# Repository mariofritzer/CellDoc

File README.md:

# CellDoc

**Diagnose für Akkuzellen.** Ein ESP32-Prüfstand, der Akkus lädt, mit konstantem Strom entlädt, dabei Kapazität, Energie und Innenwiderstand misst und am Ende eine **Lebenszahl von 0 bis 100** ausgibt. Bedient wird alles über eine Weboberfläche im Browser, am Handy wie am PC.

<picture>
  <source media="(prefers-color-scheme: dark)" srcset="docs/img/live-desktop-dark.png">
  
</picture>

> **Ausprobieren ohne Hardware:** [Demo im Browser](https://mariofritzer.github.io/CellDoc/) (Beispielwerte) · **Installieren:** [Webflasher](https://mariofritzer.github.io/CellDoc/flash/)

## Was CellDoc kann

- **Kapazitätstest** in einem Durchgang: voll laden → ruhen → mit Konstantstrom entladen → erholen → wieder voll oder auf Lagerspannung laden
- **Innenwiderstand (DC)** per Stromsprung, mehrmals während der Entladung, ausgewertet bei 100 % und 50 % Ladung
- **Lebenszahl** aus Kapazität und Innenwiderstand, mit Zelltyp-Datenbank und Schätzmodus für unbekannte Zellen
- **Zwei Anschlüsse:** A für Einzelzellen (laden und entladen), B für Packs bis 6S mit Balancer-Messung jeder Einzelzelle
- **Akkutypen:** Li-Ion, LiPo, Li-HV, LiFePO4, LTO, NiMH/NiCd und Blei
- **Bis 30 W / 8 A** Entladeleistung mit zwei Lastkanälen und Lüfter
- **Sicherheit:** drei Temperaturfühler mit Drosselung und Abschaltung, Über- und Unterspannung pro Zelle, Überstrom, Lüfter- und Sensorausfall, Not-Aus-Taste
- **Ergebnisse** mit Entladekurve, Ri-Verlauf und Vergleich zum ersten Test derselben Zelle
- **Zellenbestand** mit fester Nummer je Zelle (CD-0042), Suche nach Nummer, Name, Lagerort oder Notiz und Note A–D
- **Etiketten** mit Nummer, QR-Code und Messwerten als Bild für Etikettendrucker wie Supvan E16 oder Niimbot
- **Selbstentladungstest** über 7–14 Tage, findet Zellen mit innerem Kurzschluss
- **Pack zusammenstellen:** sucht gleich starke Zellen für z. B. 10S4P, verteilt sie gleichmäßig auf die Parallelgruppen und zeichnet einen druckbaren Bauplan mit Nickelbändern und Balancer-Abgriffen
- **Zyklentest** mit Kapazität je Zyklus, **Kurvenvergleich** mehrerer Tests und **Spannungscheck** beim Wiedereinstecken einer Zelle
- **Mehrere Geräte, ein Bestand:** CellDoc und Mini im selben WLAN teilen sich Zellen und Nummern
- **Home Assistant** über MQTT mit automatischer Erkennung, **Datensicherung** und CSV-Export
- **Handbuch** direkt im Gerät: Akkutypen, Bauformen, Stecker, Messwerte, Sicherheit, Lagerung und Entsorgung
- **Display und Taster** (optional, wie bei der Mini): Messwerte, Temperaturen, Balancer, IP-Adresse; Test starten und stoppen direkt am Gerät
- **Firmware-Updates** über den Browser, WLAN-Einrichtung direkt im Webflasher oder über einen eigenen Hotspot

## Bilder

| Live | Ergebnisse | Ergebnis im Detail |
|:---:|:---:|:---:|
|  |  |  |

| Test starten | Handbuch | Einstellungen |
|:---:|:---:|:---:|
|  |  |  |

*Fotos vom fertigen Aufbau folgen.*

## Zellenbestand und Etiketten

Jeder Test legt die Zelle mit einer festen Nummer an. Die Nummer kommt mit einem Etikettendrucker auf die Zelle, der QR-Code darauf öffnet die Zelle später direkt in CellDoc. Beim nächsten Test wird sie aus dem Bestand gewählt und automatisch mit dem ersten Test verglichen.

| Bestand | Zelle | Etikett | Pack |
|:---:|:---:|:---:|:---:|
|  |  |  |  |

- **Etiketten:** 12–15 mm breit, 30–50 mm lang, 203 dpi, reines Schwarz-Weiß. Für den **Supvan E16**: Bild speichern und in der Katasymbol-App als Bild einfügen. Für viele Zellen auf einmal gibt es eine CSV-Liste für den Tabellenimport der App.
- **QR-Code scannen:** in der Weboberfläche über die Handykamera (Foto, über HTTPS auch live) oder mit einem optionalen Scanner-Modul (GM861S) direkt am Gerät. Die Zelle öffnet sich oder wird für den nächsten Test ausgewählt. Bei der Mini landet sie im Schacht, in den sie gesteckt wird.
- **Suche:** „42“ findet CD-0042, Wörter finden Name, Lagerort, Notiz oder Pack. Filter für Note A–B, „Prüfen“, verbaut und ausgemustert.
- **Selbstentladung:** Nach einem Test mit „Danach voll laden“ merkt sich CellDoc nach einer Stunde die Spannung. Nach 7–14 Tagen nachmessen, unter 3 mV pro Tag ist gut.
- **Pack zusammenstellen:** Serie und Parallel eingeben, CellDoc sucht passende Zellen, verteilt sie so, dass jede Parallelgruppe gleich viel Kapazität hat, und markiert sie auf Wunsch als verbaut.
- **Bauplan:** zeigt für jede Zelle Platz und Richtung, die Nickelbänder auf Ober- und Unterseite und die Balancer-Abgriffe B0 bis Bn, zum Drucken oder als SVG.
- **Mehrere Geräte:** Jedes Gerät bekommt einen Namen (z. B. `celldoc` und `celldoc-mini`), die anderen werden als Partner eingetragen oder gesucht. Bestand und Nummern gleichen sich dann von selbst ab.
- **Home Assistant:** Broker unter Einstellungen → MQTT eintragen, CellDoc erscheint von selbst als Gerät mit allen Messwerten und einer Stopp-Taste.
- **Datensicherung:** Bestand, Ergebnisse und Einstellungen als Datei sichern und wieder einspielen, dazu CSV-Export für Excel.

## Hardware

**3D-Ansicht des Aufbaus** (Anordnungsvorschlag):

<picture>
  <source media="(prefers-color-scheme: dark)" srcset="docs/img/aufbau-dark.jpg">
  
</picture>

**Anschlussplan** mit allen Modulen und Kabelfarben:

<picture>
  <source media="(prefers-color-scheme: dark)" srcset="docs/img/anschlussplan-dark.jpg">
  
</picture>

<details><summary>Blockschaltbild</summary>

<picture>
  <source media="(prefers-color-scheme: dark)" srcset="docs/img/blockschaltbild-dark.png">
  
</picture>
</details>

ESP32 DevKit, 2× INA226 (Strom/Spannung), MCP4725 + LM358 + 2× IRFP250N (Konstantstromlast), TP5000 (Lader 4,2/3,6 V), 2× ADS1115 (Balancer), 3× DS18B20, zwei Relais, CPU-Kühler mit 4-Pin-Lüfter, Versorgung über USB-C (PD-Decoy auf 12 V).

Statt des ESP32 DevKit V1 geht auch ein **ESP32-S3-DevKitC-1 N16R8** (mehr Speicher, RGB-Statusleuchte). Dafür gibt es eigene Schaltpläne und Firmware-Dateien mit `-s3` im Namen. Der Webflasher erkennt den Chip selbst.

Schaltung, Pinbelegung, optionaler QR-Scanner und Einkaufsliste: **[docs/hardware.md](docs/hardware.md)**

## CellDoc Mini

Die kleine Version nur für **18650 Li-Ion**: laden, entladen, Kapazität, Innenwiderstand und Lebenszahl, in drei Größen mit **1, 2 oder 4 Schächten**, die gleichzeitig laufen. Versorgung über USB-C, ein TP4056 und eine kleine Konstantstromlast pro Schacht (2 A bzw. 1 A bei vier Schächten), optional ein OLED mit drei Tastern. Weboberfläche und Ergebnisse sind dieselben wie beim großen CellDoc.

Schaltpläne für alle drei Varianten, Stücklisten und Bedienung: **[docs/mini.md](docs/mini.md)** · [Demo Mini 4](https://mariofritzer.github.io/CellDoc/?mini=4)

## CellDoc Nano

Die kleinste Variante mit rund zwölf Teilen: **ein Schacht für 18650**, ein **ESP32-C3 SuperMini**, ein INA226, ein TP4056 und ein fester **Lastwiderstand (3 Ω)**, den die Firmware per PWM auf Konstantstrom regelt (bis 1,2 A, empfohlen 0,8 A). Strom kommt über die USB-C-Buchse des C3, bedient wird sie über die BOOT-Taste und die LED auf dem Board oder ganz normal über die Weboberfläche. Kapazität, Innenwiderstand, Lebenszahl, Bestand, Etiketten, MQTT und Sync wie bei den großen Geschwistern.

Schaltplan, Stückliste und Bedienung: **[docs/nano.md](docs/nano.md)** · [Demo Nano](https://mariofritzer.github.io/CellDoc/?nano=1)

## Firmware installieren

### Erstinstallation per USB

Am einfachsten mit dem **[CellDoc Webflasher](https://mariofritzer.github.io/CellDoc/flash/)**: ESP32 per USB anschließen, im Chrome oder Edge Gerät wählen (CellDoc, Mini 1, 2, 4 oder Nano), *Verbinden und installieren*. Er spielt immer den neuesten Stand von `main` auf.

Von Hand: unter [Releases](../../releases) die Datei **`celldoc-factory.bin`** laden (Mini: `celldoc-mini1-factory.bin`, `-mini2-` oder `-mini4-`, Nano: `celldoc-nano-factory.bin`) und mit dem [ESP Web Flasher von Espressif](https://espressif.github.io/esptool-js/) an Adresse **0x0** schreiben.

Alternativ mit PlatformIO: `pio run -t upload`

### Updates

Unter **Einstellungen → Firmware-Update** die Datei **`celldoc-firmware.bin`** hochladen (Mini: `celldoc-mini<n>-firmware.bin`, Nano: `celldoc-nano-firmware.bin`). Einstellungen und Ergebnisse bleiben erhalten.

## Erste Schritte

1. **WLAN direkt im Webflasher:** Nach der Installation fragt der [Webflasher](https://mariofritzer.github.io/CellDoc/flash/) nach dem WLAN („Connect to Wi-Fi“). Netz wählen, Passwort eingeben, fertig, „Visit Device“ öffnet die Oberfläche. Das geht auch später ohne neu zu flashen: verbinden und „Change Wi-Fi“ wählen.
   Ohne diesen Schritt öffnet CellDoc den Hotspot **CellDoc-XXXX** mit dem Passwort **`celldoc1`**. Verbinden, die Seite öffnet sich automatisch, sonst `http://192.168.4.1` aufrufen.
2. Im Hotspot unter **Einstellungen → WLAN** das Heimnetz wählen und speichern. Danach ist CellDoc unter **http://celldoc.local** oder seiner IP erreichbar.
3. **Einstellungen → Temperaturfühler**: prüfen, dass Zelle, Pack und Kühlkörper richtig zugeordnet sind.
4. **Einstellungen → Kalibrierung**: Spannung und Strom einmal mit dem Multimeter abgleichen.
5. **Live → Starten**: Zelltyp wählen, Strom einstellen, los.

## Die Lebenszahl

| Zelltyp | Gewichtung | Kapazität | Innenwiderstand |
|---|---|---|---|
| bekannt | 70 % Kapazität, 30 % Ri | 100 % Nennwert = 100 Punkte, 60 % = 0 | Neuwert = 100 Punkte, 2,5-facher Neuwert = 0 |
| unbekannt | 50 / 50 | gegen typischen Wert der Chemie | feste Grenzen pro Zelle |

Bei unbekannten Zellen zeigt CellDoc einen Bereich (z. B. „≈ 55–70 %“). Die hinterlegten Ri-Neuwerte sind Richtwerte für den DC-Innenwiderstand und lassen sich beim Start überschreiben. Die Berechnung liegt in [`src/soh.h`](src/soh.h) und wird mit [`test/test_soh.cpp`](test/test_soh.cpp) bei jedem Build geprüft.

## Selbst bauen

```bash
pip install platformio
pio run -e esp32dev            # baut Firmware und bettet web/index.html ein
pio run -e esp32dev -t upload  # flasht per USB
pio run -e mini2 -t upload     # CellDoc Mini mit 2 Schächten (mini1, mini2, mini4)
pio run -e nano -t upload      # CellDoc Nano (ESP32-C3 SuperMini)
pio device monitor             # serielle Ausgabe, 115200 Baud
```

Die Weboberfläche ist eine einzelne Datei: [`web/index.html`](web/index.html). Direkt im Browser geöffnet startet sie im Demo-Modus, praktisch zum Entwickeln ohne Gerät. Beim Bauen packt `tools/embed_web.py` sie komprimiert in die Firmware.

| Pfad | Inhalt |
|---|---|
| `src/config.h` | Pins und harte Grenzwerte |
| `src/hal.*` | Messung, Last-Regelung, Lader, Relais, Lüfter |
| `src/tester.*` | Testablauf, Ri-Messung, Sicherheitsüberwachung |
| `src/profiles.h` | Akkuchemien und Zelltypen |
| `src/soh.h` | Lebenszahl und Note |
| `src/cells.*` | Zellenbestand, Selbstentladung |
| `src/mqtt.*` | Home Assistant über MQTT |
| `src/sync.*` | gemeinsamer Bestand mehrerer Geräte |
| `src/scanner.*` | QR-Scanner-Modul |
| `src/web_data.cpp` | Bestand, Datensicherung und Uhrzeit über die REST-API |
| `src/web.*` | WLAN, REST-API, Firmware-Update |
| `src/mini/` | CellDoc Mini und Nano: Schächte, OLED, eigene Web-API (`hal_nano.cpp` = Nano-Hardware) |
| `web/index.html` | Weboberfläche inkl. Handbuch |

Jeder Push auf `main` baut die Firmware über GitHub Actions und aktualisiert die Vorabversion `latest`. Ein Tag `v1.2.3` erzeugt ein normales Release.

## Status

Firmware und Weboberfläche sind vollständig, **auf echter Hardware aber noch nicht erprobt**. Vor dem ersten Test mit wertvollen Akkus bitte mit einer günstigen Zelle und kleinem Strom anfangen und die Werte mit einem Multimeter vergleichen.

## Sicherheit

Lithium-Akkus können bei Fehlern brennen. Tests mit hohen Strömen und LiPo-Packs nur auf nicht brennbarer Unterlage und nicht unbeaufsichtigt durchführen. Die Schutzfunktionen der Firmware ersetzen keine Aufsicht. Nachbau und Nutzung auf eigene Verantwortung.

## Lizenz

[MIT](LICENSE) © 2026 Mario Fritzer. Der eingebaute QR-Leser ist [jsQR](https://github.com/cozmo/jsQR) (Apache-2.0).

Die Idee geht auf das *ESP32 Smart Battery Dashboard* von LifeTronix zurück. Hardwarekonzept, Firmware und Oberfläche von CellDoc sind eigenständig neu entwickelt.

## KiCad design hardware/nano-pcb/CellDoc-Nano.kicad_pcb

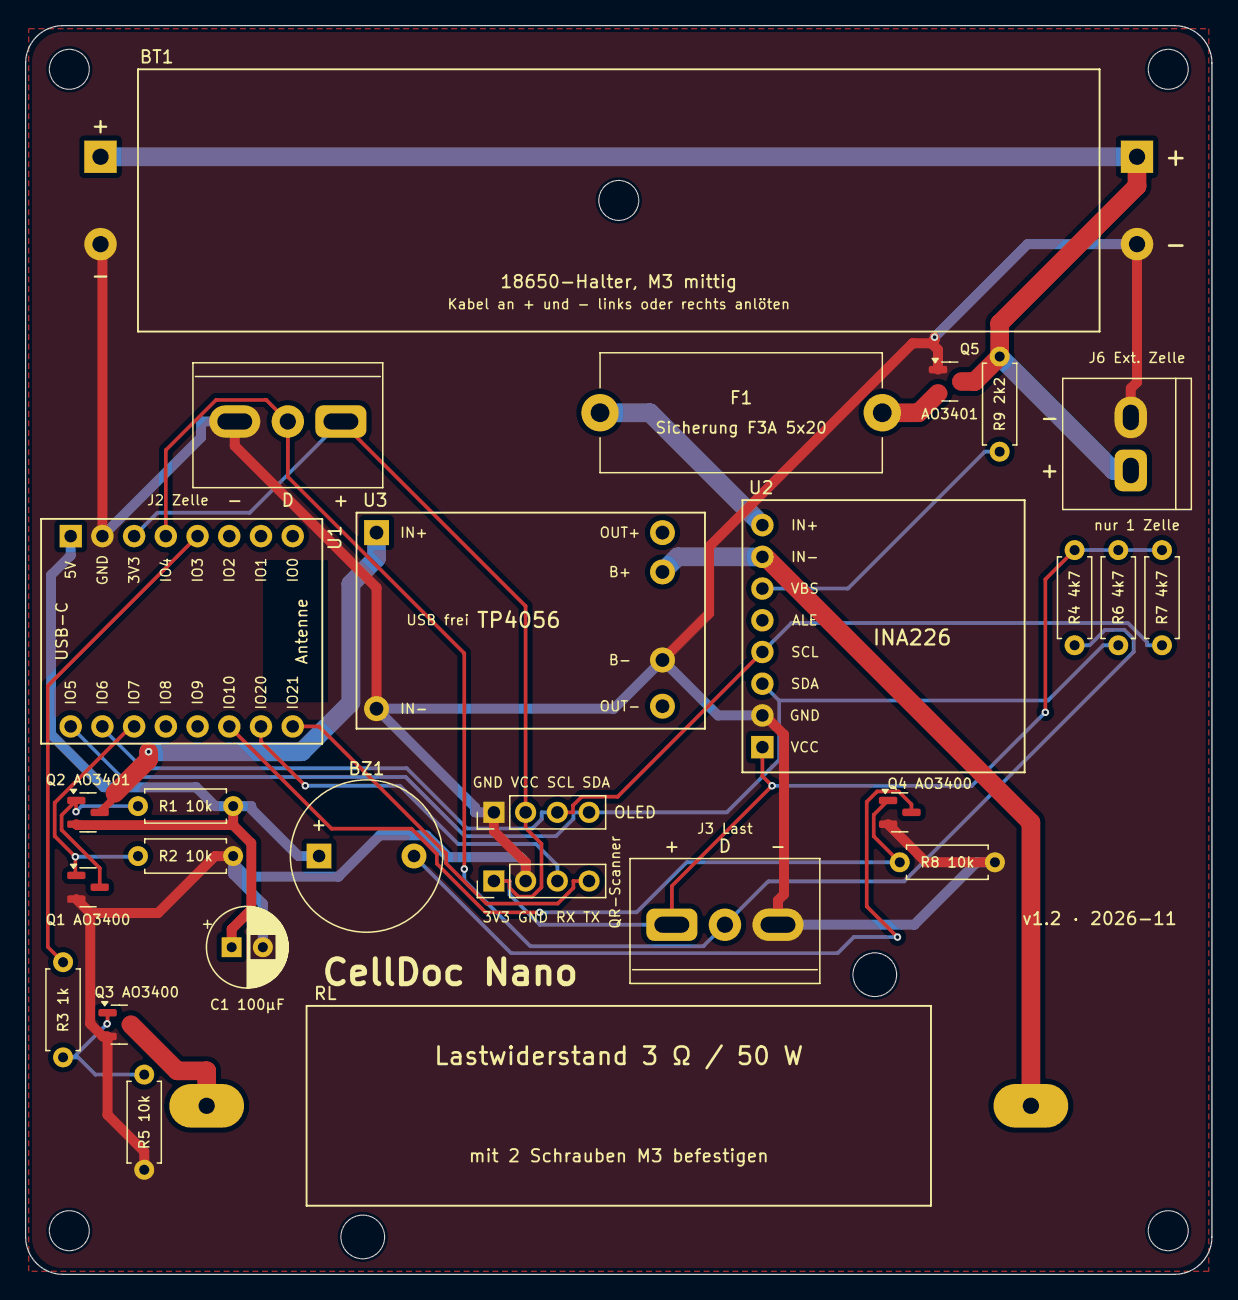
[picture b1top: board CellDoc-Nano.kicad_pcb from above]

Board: 2 copper layers, 95.0 x 100.0 mm, 31 parts (0 on the bottom side), 21 nets.

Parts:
BT1: 18650-Halter; 18650_Halter_Kabel
BZ1: Summer 5V; Buzzer_12x9.5RM7.6
C1: 100uF 10V; CP_Radial_D6.3mm_P2.50mm
F1: Sicherung F3A 5x20; Fuseholder_Cylinder-5x20mm_Stelvio-Kontek_PTF78_Horizontal_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
H1, H2, H3, H4: MountingHole_3.2mm_M3
J2: DS18B20 Zelle; Klemme_3pol_3.5_oder_5mm
J3: DS18B20 Last opt.; Klemme_3pol_3.5_oder_5mm
J4: OLED opt.; PinHeader_1x04_P2.54mm_Vertical
J5: QR GM861S opt.; PinHeader_1x04_P2.54mm_Vertical
J6: Ext. Zelle; Klemme_2pol_3.5_oder_5mm
Q1, Q3, Q4: AO3400; SOT-23
Q2, Q5: AO3401; SOT-23
R1, R2, R5, R8: 10k; R_Axial_DIN0207_L6.3mm_D2.5mm_P7.62mm_Horizontal
R3: 1k; R_Axial_DIN0207_L6.3mm_D2.5mm_P7.62mm_Horizontal
R4: 4k7; R_Axial_DIN0207_L6.3mm_D2.5mm_P7.62mm_Horizontal
R6, R7: 4k7 opt.; R_Axial_DIN0207_L6.3mm_D2.5mm_P7.62mm_Horizontal
R9: 2k2; R_Axial_DIN0207_L6.3mm_D2.5mm_P7.62mm_Horizontal
RL: 3R 50W; Lastwiderstand_50W_Alu
U1: ESP32-C3 SuperMini; ESP32-C3_SuperMini
U2: INA226 (Shunt R010); INA226_CJMCU-226
U3: TP4056 USB-C; TP4056_USB-C_Protected

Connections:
+3V3: J2.1, J3.1, J4.2, J5.1, R4.1, R6.1, R7.1, U1.3V3, U2.VCC
+5V: BZ1.1, C1.1, Q2.2, R1.2, U1.5V
BAT+: BT1.+, J6.1, Q5.3, R9.1
BAT_F: F1.2, U2.IN+
BAT_P: F1.1, Q5.2
BUZZER: Q4.1, R8.1, U1.10
BZ_N: BZ1.2, Q4.3
CELL: RL.2, U2.IN-, U3.B+
CHG: Q1.1, R2.1, U1.7
GND: BT1.-, C1.2, J2.3, J3.3, J4.1, J5.2, J6.2, Q1.2, Q3.2, Q4.2, Q5.1, R2.2, R5.2, R8.2, U1.GND, U2.GND, U3.B-, U3.IN-
LOAD_D: Q3.3, RL.1
LOAD_G: Q3.1, R3.2, R5.1
LOAD_PWM: R3.1, U1.3
ONEWIRE: J2.2, J3.2, R4.2, U1.4
Q2_G: Q1.3, Q2.1, R1.1
SCAN_RX: J5.3, U1.20
SCAN_TX: J5.4, U1.21
SCL: J4.3, R7.2, U1.6, U2.SCL
SDA: J4.4, R6.2, U1.5, U2.SDA
TP_IN: Q2.3, U3.IN+
VBS_IN: R9.2, U2.VBS

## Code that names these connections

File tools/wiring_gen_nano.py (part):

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gn, dn, sn = nmos(240, 520, "Q1", "AO3400", side="r")
wire(dn, (dn[0], 466), (220, 466), (220, 400))
gnd(*sn)
wire((140, 520), gn); label(140, 520, "CHG", "r")
dot(180, 520); res_v(180, 520, 600, "R2", "10 kΩ", "l"); gnd(180, 600)
# TP4056-Modul
tx = 420
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t(tx + 75, 446, "4,2 V", 10, PINNAME, "middle")
p = pin(tx, 430, "l", "IN+", 1); wire(sp_, p)
p = pin(tx, 480, "l", "IN−", 2); wire(p, (tx - 40, 480)); gnd(tx - 40, 480)
p = pin(tx + 150, 400, "r", "B+", 3); pwire(p, (640, 400)); label(640, 400, "CELL", "l")
p = pin(tx + 150, 480, "r", "B−", 4); wire(p, (610, 480)); gnd(610, 480)
for k, s_ in enumerate([
        "USB-C-Buchse am TP4056 bleibt frei.",
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# ---------------------------------------------------------------- Temperatur
section(50, 656, 690, 900, "Temperatur (DS18B20, TO-92 oder wasserdicht)")
wire((110, 720), (400, 720)); pwr(110, 720, "+3V3", "l")
wire((110, 770), (400, 770)); label(110, 770, "ONEWIRE", "r")
res_v(400, 720, 770, "R4", "4,7 kΩ", "r")
dot(400, 720); dot(400, 770)
for k, (ref, where, dash) in enumerate([("U4", "Zelle", False), ("U5", "Lastwiderstand (opt.)", True)]):
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p = pin(150, 1002, "r", None, None, L=40)
g, dr, sr = nmos(180, 1100, "Q4", "AO3400")
wire(p, (dr[0], 1002), dr); gnd(*sr)
wire((100, 1100), g); label(100, 1100, "BUZZER", "r")
# OLED
box(330, 966, 110, 100)
o.append(f'<rect x="345" y="980" width="56" height="34" fill="#e9e6da" stroke="{COMP}" stroke-width="1"/>')
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p = pin(ux, 268, "l", "SDA", 5); wire(p, (ux - 70, 268)); label(ux - 70, 268, "SDA", "r")
p = pin(ux, 298, "l", "SCL", 6); wire(p, (ux - 70, 298)); label(ux - 70, 298, "SCL", "r")
p = pin(ux + 130, 140, "r", "IN−", 7); pwire(p, (1700, 140)); dot(1660, 140)
wire((1660, 140), (1660, 104)); label(1660, 104, "CELL", "r")
# Last: RL von CELL nach Drain Q3
pwire((1700, 140), (1800, 140), (1800, 190))
res_v(1800, 190, 290, "RL", "3 Ω / 50 W", "r", w=3.4)
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pwire(sl, (sl[0], 430)); gnd(sl[0], 430)
dot(1730, 360); wire((1730, 360), gl)
res_h(1640, 1730, 360, "R3", "1 kΩ")
wire((1600, 360), (1640, 360)); label(1600, 360, "LOAD_PWM", "l")
res_v(1730, 360, 440, "R5", "10 kΩ", "l"); gnd(1730, 440)
for k, s_ in enumerate([
        "Q3 schaltet RL mit 10 kHz. Der INA226 mittelt über",
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
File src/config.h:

// CellDoc – Pinbelegung und feste Grenzwerte
// Passt zur Hardware-Beschreibung in docs/hardware.md
#pragma once
#include <Arduino.h>

#ifndef CELLDOC_VERSION
#define CELLDOC_VERSION "dev"
#endif

namespace cfg {

// ---------- Pins ----------
#if CONFIG_IDF_TARGET_ESP32C3
// ESP32-C3 SuperMini (nur CellDoc Nano, übrige Pins in src/mini/config_mini.h)
constexpr uint8_t PIN_SCAN_RX    = 20;  // vom TX des Scanners
constexpr uint8_t PIN_SCAN_TX    = 21;  // zum RX des Scanners
constexpr int8_t  PIN_RGB        = -1;
#elif CONFIG_IDF_TARGET_ESP32S3
// ESP32-S3-DevKitC-1 (N16R8): IO35–37 gehören zum PSRAM, IO19/20 zu USB, IO0/3/45/46 sind Boot-Pins
constexpr uint8_t PIN_SDA        = 8;
constexpr uint8_t PIN_SCL        = 9;
constexpr uint8_t PIN_ONEWIRE    = 4;
constexpr uint8_t PIN_LOAD_EN_N  = 5;
constexpr uint8_t PIN_RELAY_K1   = 6;
constexpr uint8_t PIN_RELAY_K2   = 7;
constexpr uint8_t PIN_CHG_CS_HI  = 15;
constexpr uint8_t PIN_CHG_CS_LO  = 16;
constexpr uint8_t PIN_CHG_CHRG   = 17;
constexpr uint8_t PIN_CHG_STDBY  = 18;
constexpr uint8_t PIN_FAN_PWM    = 10;
constexpr uint8_t PIN_FAN_TACH   = 11;
constexpr uint8_t PIN_BUZZER     = 12;
constexpr uint8_t PIN_BUTTON     = 0;
constexpr uint8_t PIN_SCAN_RX    = 13;
constexpr uint8_t PIN_SCAN_TX    = 14;
constexpr int8_t  PIN_RGB        = 48;  // RGB-LED auf dem Board (WS2812)
constexpr uint8_t PIN_BTN_PREV   = 1;   // Taster gegen GND (optional, interne Pull-ups)
constexpr uint8_t PIN_BTN_OK     = 2;
constexpr uint8_t PIN_BTN_NEXT   = 42;
#else
constexpr uint8_t PIN_SDA        = 21;
constexpr uint8_t PIN_SCL        = 22;
constexpr uint8_t PIN_ONEWIRE    = 4;
constexpr uint8_t PIN_LOAD_EN_N  = 16;  // LOW = Last frei (BSS138 gibt Sollwert und Gates frei)
constexpr uint8_t PIN_RELAY_K1   = 26;  // Laderelais, HIGH = Lader an Anschluss A
constexpr uint8_t PIN_RELAY_K2   = 27;  // Lastumschaltung, LOW = A (NC), HIGH = B (NO)
constexpr uint8_t PIN_CHG_CS_HI  = 32;  // HIGH = CS auf VIN = 4,2 V
constexpr uint8_t PIN_CHG_CS_LO  = 33;  // HIGH = CS auf GND = Lader aus
constexpr uint8_t PIN_CHG_CHRG   = 34;  // LOW = lädt
constexpr uint8_t PIN_CHG_STDBY  = 35;  // LOW = voll
constexpr uint8_t PIN_FAN_PWM    = 25;  // über AO3400, Signal invertiert
constexpr uint8_t PIN_FAN_TACH   = 39;
constexpr uint8_t PIN_BUZZER     = 17;
constexpr uint8_t PIN_BUTTON     = 0;   // BOOT-Taste = Not-Aus
// QR-Scanner (optional, GM861S, 3,3 V, 9600 Baud) – gleiche Pins bei CellDoc und Mini
constexpr uint8_t PIN_SCAN_RX    = 19;  // vom TX des Scanners
constexpr uint8_t PIN_SCAN_TX    = 18;  // zum RX des Scanners
constexpr int8_t  PIN_RGB        = -1;
constexpr uint8_t PIN_BTN_PREV   = 13;  // Taster gegen GND (optional, interne Pull-ups)
constexpr uint8_t PIN_BTN_OK     = 14;
constexpr uint8_t PIN_BTN_NEXT   = 23;
#endif

// ---------- I2C-Adressen ----------
constexpr uint8_t ADDR_INA_A   = 0x40;
constexpr uint8_t ADDR_INA_B   = 0x41;
constexpr uint8_t ADDR_DAC     = 0x60;
constexpr uint8_t ADDR_ADS_1   = 0x48;  // Balancer-Abgriffe 1–4
constexpr uint8_t ADDR_ADS_2   = 0x49;  // Balancer-Abgriffe 5–6
constexpr uint8_t ADDR_OLED    = 0x3C;  // SH1106 1,3" (optional)

// ---------- Messkette ----------
constexpr float SHUNT_OHM        = 0.010f;   // INA226-Shunt A und B
constexpr float LOAD_SENSE_OHM   = 0.10f;    // je Lastkanal
constexpr uint8_t LOAD_CHANNELS  = 2;
constexpr float DAC_DIVIDER      = 8.5f;     // 7,5 kΩ / 1 kΩ
constexpr float DAC_VREF         = 3.3f;
constexpr float BAL_DIVIDER      = 11.0f;    // 100 kΩ / 10 kΩ
constexpr uint8_t BAL_TAPS       = 6;

// ---------- Harte Grenzen (nicht per Weboberfläche änderbar) ----------
constexpr float MAX_POWER_W      = 30.0f;
constexpr float MAX_CURRENT_A    = 8.0f;
constexpr float MAX_CURRENT_PORT_A = 5.0f;   // Einzelzelle, F1 = 7,5 A
constexpr float MAX_PACK_V       = 26.0f;    // 6S voll + Reserve
constexpr float ABS_MIN_CELL_V   = 2.0f;     // darunter wird nie entladen
constexpr float OVERCURRENT_FACTOR = 1.25f;
constexpr uint32_t OVERCURRENT_MS  = 300;
constexpr float SINK_STOP_C      = 90.0f;
constexpr float SINK_WARN_C      = 75.0f;

// ---------- Zeitraster ----------
constexpr uint32_t INA_PERIOD_MS  = 40;
constexpr uint32_t TEMP_PERIOD_MS = 1000;
constexpr uint32_t CHG_THROTTLE_PERIOD_MS = 10000;

// ---------- Netzwerk ----------
constexpr const char* AP_PASSWORD = "celldoc1";
constexpr const char* HOSTNAME    = "celldoc";

}  // namespace cfg
